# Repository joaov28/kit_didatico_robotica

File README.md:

# Desenvolvimento de um kit de robótica de baixo custo voltado ao ensino no IFSC
**Autor:** João Vitor Bassani
\
\
\
Dialogar sobre o futuro da tecnologia e seu impacto no desenvolvimento educacional é um debate urgente e necessário, que envolve fatores políticos, econômicos e sociais complexos. Enquanto o mundo tende a uma realidade completamente imersa em soluções tecnológicas para problemas cotidianos, as instituições de ensino brasileiras veem-se rodeadas por condições inviáveis para execução dos seus planos de ensino e para o desenvolvimento humano básico que é encontrado em ambientes pedagógicos. Toda essa situação se constroi como reflexo da escassez de recursos e de uma construção social de grandes disparidades socioeconômicas e barreiras culturais, capazes de atrapalhar o ingresso e a permanência dos estudantes aptos para o ensino, resultando principalmente na marginalização destes indivíduos.
 
 Neste estudo, numa busca pelo entendimento do panorama atual do ensino superior e das condições que direcionam os estudantes a esses ambientes, o foco principal é traçar uma alternativa viável capaz de interferir nessas realidades e sugerir uma solução simples e acessível que permita a aproximação do ensino de robótica a todos os cenários e níveis de aprendizado, procurando por recursos que tenham viabilidade em aspecto construtivo e econômico.
 
 A ideia geral para o projeto apresentado é proporcionar um documento de referência que descreva a construção de um \textit{kit} de iniciação ao estudo da robótica, focando na acessibilidade às informações disponibilizadas e em um alto índice de reprodutibilidade, contendo componentes fáceis de acessar, mesmo em um país com poucos recursos tecnológicos, e dependendo apenas do uso de ferramentas gratuitas de desenvolvimento. Ao longo dos capítulos, o trabalho descreve a construção de uma plataforma personalizada de \textit{hardware}, acompanhada de um programa completo, embarcado em seu núcleo microcontrolado, que permite o gerenciamento das funções principais estabelecidas ao longo da pesquisa e estudo inicial.
 
 Todo o desenvolvimento do texto é focado na apresentação de cada detalhe de decisão sobre os aspectos construtivos do conjunto, permitindo que em ações posteriores possa-se entender a progressão das alterações realizadas, ou mesmo incentivar a personalização de todos estes pontos, garantindo que além de poder reproduzir nos moldes propostos, o usuário possa inspirar-se a criar uma solução que se adapte à sua própria realidade.

**Palavras-chave:** Robótica Educacional, Kit didático, Robótica Pedagógica Livre.
\
\
\
\
Trabalho de conclusão de curso submetido ao Instituto Federal de Educação, Ciência e Tecnologia de Santa Catarina (IFSC) como parte dos requisitos para obtenção do título de engenheiro eletrônico. Florianópolis, Novembro de 2020.

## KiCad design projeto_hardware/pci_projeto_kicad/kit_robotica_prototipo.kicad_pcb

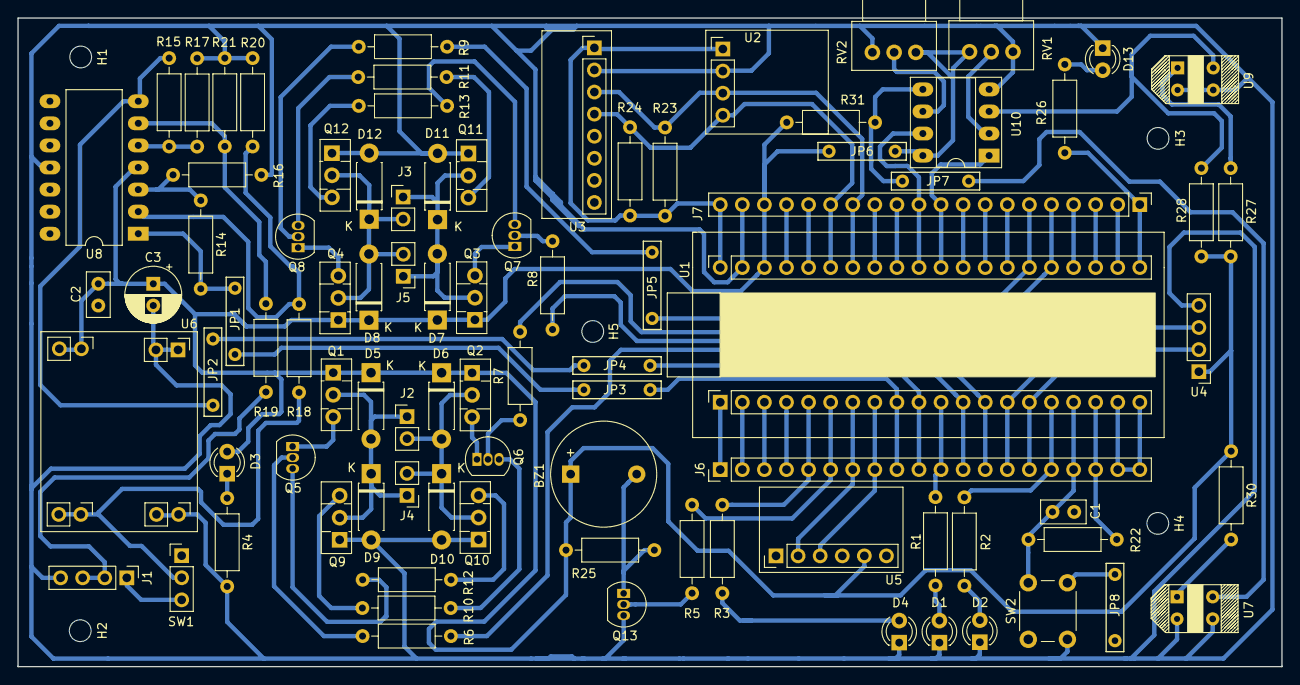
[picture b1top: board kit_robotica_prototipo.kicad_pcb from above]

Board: 2 copper layers, 145.4 x 74.6 mm, 94 parts (0 on the bottom side), 83 nets.

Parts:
BZ1: Buzzer; Buzzer_12x9.5RM7.6
C1, C2: 100n; C_Disc_D5.0mm_W2.5mm_P2.50mm
C3: 1uF; CP_Radial_D6.3mm_P2.50mm
D1: LED_A; LED_D3.0mm
D2: LED_B; LED_D3.0mm
D3: LED_ON; LED_D3.0mm
D4: LED_C; LED_D3.0mm
D5, D6, D7, D8, D9, D10, D11, D12: D; D_DO-41_SOD81_P7.62mm_Horizontal
D13: LED_LOW; LED_D3.0mm
H1, H2, H3, H4, H5: MountingHole; MountingHole_2.5mm
J1: Conn_01x04; PinHeader_1x04_P2.54mm_Vertical
J2, J3, J4, J5: 01x02; PinHeader_1x02_P2.54mm_Vertical
J6, J7: Conn_01x20; PinHeader_1x20_P2.54mm_Vertical
JP1, JP2, JP3, JP4, JP5, JP6, JP7, JP8: Jumper; Jumper_7.62mm
Q1, Q2, Q3, Q4: BD140; TO-126-3_Vertical
Q5, Q6, Q7, Q8, Q13: BC548; TO-92_Inline
Q9, Q10, Q11, Q12: BD139; TO-126-3_Vertical
R1, R2, R3, R4, R5, R26, R27, R30: 1K; R_Axial_DIN0207_L6.3mm_D2.5mm_P10.16mm_Horizontal
R6, R7, R8, R9: 470R; R_Axial_DIN0207_L6.3mm_D2.5mm_P10.16mm_Horizontal
R10, R11, R12, R13: 150R; R_Axial_DIN0207_L6.3mm_D2.5mm_P10.16mm_Horizontal
R14, R15, R20, R21, R22, R28, R31: 10K; R_Axial_DIN0207_L6.3mm_D2.5mm_P10.16mm_Horizontal
R16, R18: 30K; R_Axial_DIN0207_L6.3mm_D2.5mm_P10.16mm_Horizontal
R17, R19: 15K; R_Axial_DIN0207_L6.3mm_D2.5mm_P10.16mm_Horizontal
R23, R24: 2K2; R_Axial_DIN0207_L6.3mm_D2.5mm_P10.16mm_Horizontal
R25: 100R; R_Axial_DIN0207_L6.3mm_D2.5mm_P10.16mm_Horizontal
RV1, RV2: POT; Potentiometer_Alps_RK09Y11_Single_Horizontal
SW1: SW_SPDT; PinHeader_1x03_P2.54mm_Vertical
SW2: Push_Button; SW_PUSH_6mm
U1: BluePill_STM32F103C; Bluepill_STM32F103
U2: BMP180
U3: GY-521
U4: HC-SR04; PinHeader_1x04_P2.54mm_Vertical
U5: HC-05; HC05
U6: StepDown_DC_DC
U7, U9: TCRT5000
U8: LM324; DIP-14_W10.16mm_LongPads
U10: LM393; DIP-8_W7.62mm_Socket_LongPads

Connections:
+3.3V: J6.18, J7.20, R22.1, R23.1, R24.1, U1.18, U1.40, U2.1, U3.1
+5V: BZ1.1, C2.1, C3.1, D3.2, D5.1, D6.1, D7.1, D8.1, J7.18, JP6.1, JP6.2, Q1.1, Q2.1, Q3.1, Q4.1, R25.1, R27.1, R28.1, R30.1, R31.1, RV1.3, RV2.1, U1.38, U4.1, U5.5, U6.3, U6.4, U8.4, U10.8
A2: J6.9, JP3.1, U1.9
A3: J6.10, JP4.2, U1.10
BATT+: R18.2, SW1.2, U6.5, U6.6
BATT_MED: J1.2, J1.3, R19.1
D1: J6.15, U1.15, U4.2
D2: J6.14, U1.14, U4.3
D3: J6.11, R1.2, U1.11
D4: J6.16, R2.2, U1.16
D5: J6.5, R3.2, U1.5
D6: J7.1, R26.2, U1.21
GND: C1.2, C2.2, C3.2, D1.1, D2.1, D4.1, D9.2, D10.2, D11.2, D12.2, D13.1, J1.4, J6.19, J6.20, J7.19, JP8.1, JP8.2, Q9.1, Q10.1, Q11.1, Q12.1, Q13.3, R4.2, R16.1, R17.2, R20.2, R21.2, RV1.1, RV2.3, SW2.2, U1.19, U1.20, U1.39, U2.2, U3.2, U3.7, U4.4, U5.4, U6.1, U6.2, U6.7, U6.8, U7.2, U7.3, U8.11, U9.2, U9.3, U10.4
I2C_SCL1: J7.14, R23.2, U1.34, U2.3, U3.3
I2C_SDA1: J7.15, R24.2, U1.35, U2.4, U3.4
NRST: C1.1, J6.17, R22.2, SW2.1, U1.17
unnamed: BZ1.2, Q13.1, R25.2
unnamed: D1.2, R1.1
unnamed: D2.2, R2.1
unnamed: D3.1, R4.1
unnamed: D4.2, R3.1
unnamed: D5.2, D9.1, J2.1, J4.1, Q1.2, Q9.2
unnamed: D6.2, D10.1, J2.2, J4.2, Q2.2, Q10.2
unnamed: D7.2, D11.1, J3.1, J5.1, Q3.2, Q11.2
unnamed: D8.2, D12.1, J3.2, J5.2, Q4.2, Q12.2
unnamed: D13.2, R26.1
unnamed: J1.1, SW1.3
unnamed: JP1.1, JP3.2
unnamed: JP1.2, R14.2, U8.1
unnamed: JP2.1, R15.2, U8.7
unnamed: JP2.2, JP4.1
unnamed: JP5.1, R9.1
unnamed: JP7.1, R31.2, U10.5
unnamed: JP7.2, U7.4
unnamed: Q1.3, Q5.1
unnamed: Q2.3, Q6.1
unnamed: Q3.3, Q7.1
unnamed: Q4.3, Q8.1
unnamed: Q5.2, R6.1
unnamed: Q5.3, R12.2
unnamed: Q6.2, R7.2
unnamed: Q6.3, R10.1
unnamed: Q7.2, R8.1
unnamed: Q7.3, R13.2
unnamed: Q8.2, R9.2
unnamed: Q8.3, R11.1
unnamed: Q9.3, R10.2
unnamed: Q10.3, R12.1
unnamed: Q11.3, R11.2
unnamed: Q12.3, R13.1
unnamed: Q13.2, R5.1
unnamed: R14.1, R16.2, U8.3
unnamed: R15.1, R17.1, U8.5
unnamed: R18.1, R20.1, U8.2
unnamed: R19.2, R21.1, U8.6
unnamed: R27.2, U9.1
unnamed: R28.2, U9.4, U10.3
unnamed: R30.2, U7.1
unnamed: RV1.2, U10.2
unnamed: RV2.2, U10.6
PA10: J7.7, U1.27
PB4: J7.12, U1.32
PB5: J7.13, U1.33
PB8: J7.16, U1.36
PB9: J7.17, U1.37
PB13: J7.2, U1.22
PB14: J7.3, U1.23
PB15: J7.4, U1.24
PC13: J6.2, U1.2
PC14: J6.3, U1.3
PC15: J6.4, U1.4
PWM1: J7.5, R7.1, U1.25
PWM1N: J6.12, R6.2, U1.12
PWM2: J7.6, JP5.2, U1.26
PWM2N: J6.13, R8.2, U1.13
PWM_BZ: J6.6, R5.2, U1.6
SERIAL_RX1: J6.8, U1.8, U5.3
SERIAL_TX1: J6.7, U1.7, U5.2
TCRT_LF: J7.10, U1.30, U10.1
TCRT_RG: J7.11, U1.31, U10.7
USBD+: J7.9, U1.29
USBD-: J7.8, U1.28
VBAT: J6.1, U1.1

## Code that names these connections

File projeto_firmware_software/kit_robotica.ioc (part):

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Mcu.Name=STM32F103C(8-B)Tx
Mcu.Package=LQFP48
Mcu.UserName=STM32F103C8Tx
PA0-WKUP.GPIOParameters=GPIO_Label
PA0-WKUP.GPIO_Label=D5
PA0-WKUP.Signal=GPIO_Output
PA1.GPIOParameters=GPIO_ModeDefaultPP,GPIO_Label
PA1.GPIO_Label=PWM_BZ
PA1.GPIO_ModeDefaultPP=GPIO_MODE_AF_PP
PA1.Signal=S_TIM2_CH2
PA13.Mode=Serial_Wire
PA13.Signal=SYS_JTMS-SWDIO
PA14.Mode=Serial_Wire
PA14.Signal=SYS_JTCK-SWCLK
PA15.GPIOParameters=GPIO_PuPd,GPIO_Label
PA15.GPIO_Label=TCRT_LF
PA15.GPIO_PuPd=GPIO_PULLUP
PA15.Signal=GPIO_Input
PA2.Mode=Asynchronous
PA2.Signal=USART2_TX
PA3.Mode=Asynchronous
PA3.Signal=USART2_RX
PA4.GPIOParameters=GPIO_Label
PA4.GPIO_Label=A2
PA4.Signal=ADCx_IN4
PA5.GPIOParameters=GPIO_Label
PA5.GPIO_Label=A3
PA5.Signal=ADCx_IN5
PA6.GPIOParameters=GPIO_Label
PA6.GPIO_Label=D3
PA6.Signal=GPIO_Output
PA7.Mode=PWM Generation1 CH1 CH1N
PA7.Signal=TIM1_CH1N
PA8.Signal=S_TIM1_CH1
PA9.Signal=S_TIM1_CH2
PB0.Mode=PWM Generation2 CH2 CH2N
PB0.Signal=TIM1_CH2N
PB1.Signal=S_TIM3_CH4
PB10.GPIOParameters=GPIO_Label
PB10.GPIO_Label=TRIG
PB10.Signal=GPIO_Output
PB11.GPIOParameters=GPIO_Label
PB11.GPIO_Label=D4
PB11.Signal=GPIO_Output
PB12.GPIOParameters=GPIO_Label
PB12.GPIO_Label=D6
PB12.Signal=GPIO_Output
PB3.GPIOParameters=GPIO_PuPd,GPIO_Label
PB3.GPIO_Label=TCRT_RG
PB3.GPIO_PuPd=GPIO_PULLUP
PB3.Signal=GPIO_Input
PB6.Mode=I2C
PB6.Signal=I2C1_SCL
PB7.Mode=I2C
PB7.Signal=I2C1_SDA
PC13-TAMPER-RTC.GPIOParameters=GPIO_Label,GPIO_ModeDefaultOutputPP
PC13-TAMPER-RTC.GPIO_Label=BUILTIN_LED
PC13-TAMPER-RTC.GPIO_ModeDefaultOutputPP=GPIO_MODE_OUTPUT_PP
PC13-TAMPER-RTC.Signal=GPIO_Output
RCC.SYSCLKFreq_VALUE=64000000
RCC.SYSCLKSource=RCC_SYSCLKSOURCE_PLLCLK
board=custom

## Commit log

2020-11-21 Adição dos arquivos produzidos durante o projeto
